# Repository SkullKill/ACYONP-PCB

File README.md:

# ACYONP-PCB
PCB for Access Control Yubikey OTP NFC Pi (ACYONP). For Raspberry Pi. This is a **Door Access Control using Electronic Door Strike, with Yubikey OTP via NFC / KeyPad / WebInterface for Authentication.**

Web interface shows the status of the whole system, along with the ability to enter pin/password/yubikey OTP string for authentication to unlock the door

Uses Inturrupt and Threads to minimise overhead, and to be non blocking as much as possible.

All options are completely customizable through the ini config file

The script [ACYONP](https://github.com/SkullKill/ACYONP) is design specificly for the Raspberry Pi.

SKaccess by Simon Kong

https://www.skaccess.com

ACYONP-SMD-01.jpg
NFC Reader is at the top of the Box, inside. putting the yubikey on top of the box will scan the yubikey neo / yubikey 5 nfc.

ACYONP-webinterface-01.jpg

## V 1.0 21/05/2019 - Initial Release

  ------------------------------------------------------------
## PCB Board Used

Ready to use PCB Board

https://www.skstore.com.au/electronics/pcb/ACYONP

PCB Design Files / gerber files

[ACYONP-PCB](https://github.com/SkullKill/ACYONP-PCB)

FYI Gerber files are in the release section

https://github.com/SkullKill/ACYONP-PCB/releases

more pictures in the wiki

https://github.com/SkullKill/ACYONP-PCB/wiki

ACYONP-SMD-Front-Red-RT-V1.2.jpg

ACYONP-SMD-Back-Red-V1.2.jpg

  ------------------------------------------------------------
## Schematics

ACYONP-SMD-schematics-v1.2a.jpg

------------------------------------------------------------
## Code Used

[ACYONP](https://github.com/SkullKill/ACYONP)

------------------------------------------------------------
## Product Used (not included)

### Dupont kit / Jumper Wires
you will need a dupont crimp kit 2.54 / tool
and / or jumper wires

e.g

Crimping Tool: 0.1-1.0 mm² Capacity, 16-28 AWG
https://www.pololu.com/product/1928

Crimp Connector Housings
https://www.pololu.com/category/70/crimp-connector-housings

Female Crimp Pins for 0.1" Housings
https://www.pololu.com/product/1930

Male Crimp Pins for 0.1" Housings
https://www.pololu.com/product/1931

Wires with Pre-Crimped Terminals
https://www.pololu.com/category/71/wires-with-pre-crimped-terminals

Premium Jumper Wires
https://www.pololu.com/category/65/premium-jumper-wires

https://www.futurlec.com/ConnHead.shtml

### Keypad

Metallic Waterproof 3x4 Keypad
https://www.futurlec.com/Keypads.shtml

### PN532 NFC controller in UART mode

e.g

https://www.dfrobot.com/product-892.html

https://wiki.dfrobot.com/NFC_Module_for_Arduino__SKU_DFR0231_

### Yubico Yubikey
YubiKey 5 NFC

https://www.yubico.com/product/yubikey-5-nfc

### other items used, can be any other ones.

H0307 • 145Lx105Wx65Dmm IP65 Sealed ABS Enclosure

https://www.altronics.com.au/p/h0307-ritec-145lx105wx65dmm-ip65-sealed-abs-enclosure/

H0151 • UB1 (157Lx95Wx53Hmm) Grey ABS Jiffy Box

https://www.altronics.com.au/p/h0151-ub1-157lx95wx53hmm-grey-abs-jiffy-box/

P0628 • 2.1mm Female Plastic Chassis Mount DC Power Socket (not necessary)

https://www.altronics.com.au/p/p0628-2.1mm-female-plastic-chassis-mount-dc-power-socket/

H1554 • 5mm LED Mounts Pk 100

https://www.altronics.com.au/p/h1554-5mm-led-mounts-pk-100/

S6109 • 1.5-24V Piezo Chassis Mount Buzzer (status buzzer)

https://www.altronics.com.au/p/s6109-1.5-24v-piezo-chassis-mount-buzzer/

S6100 • 3-15V Mechanical Chassis Mount Buzzer (door buzzer)

https://www.altronics.com.au/p/s6100-3-15v-mechanical-chassis-mount-buzzer/

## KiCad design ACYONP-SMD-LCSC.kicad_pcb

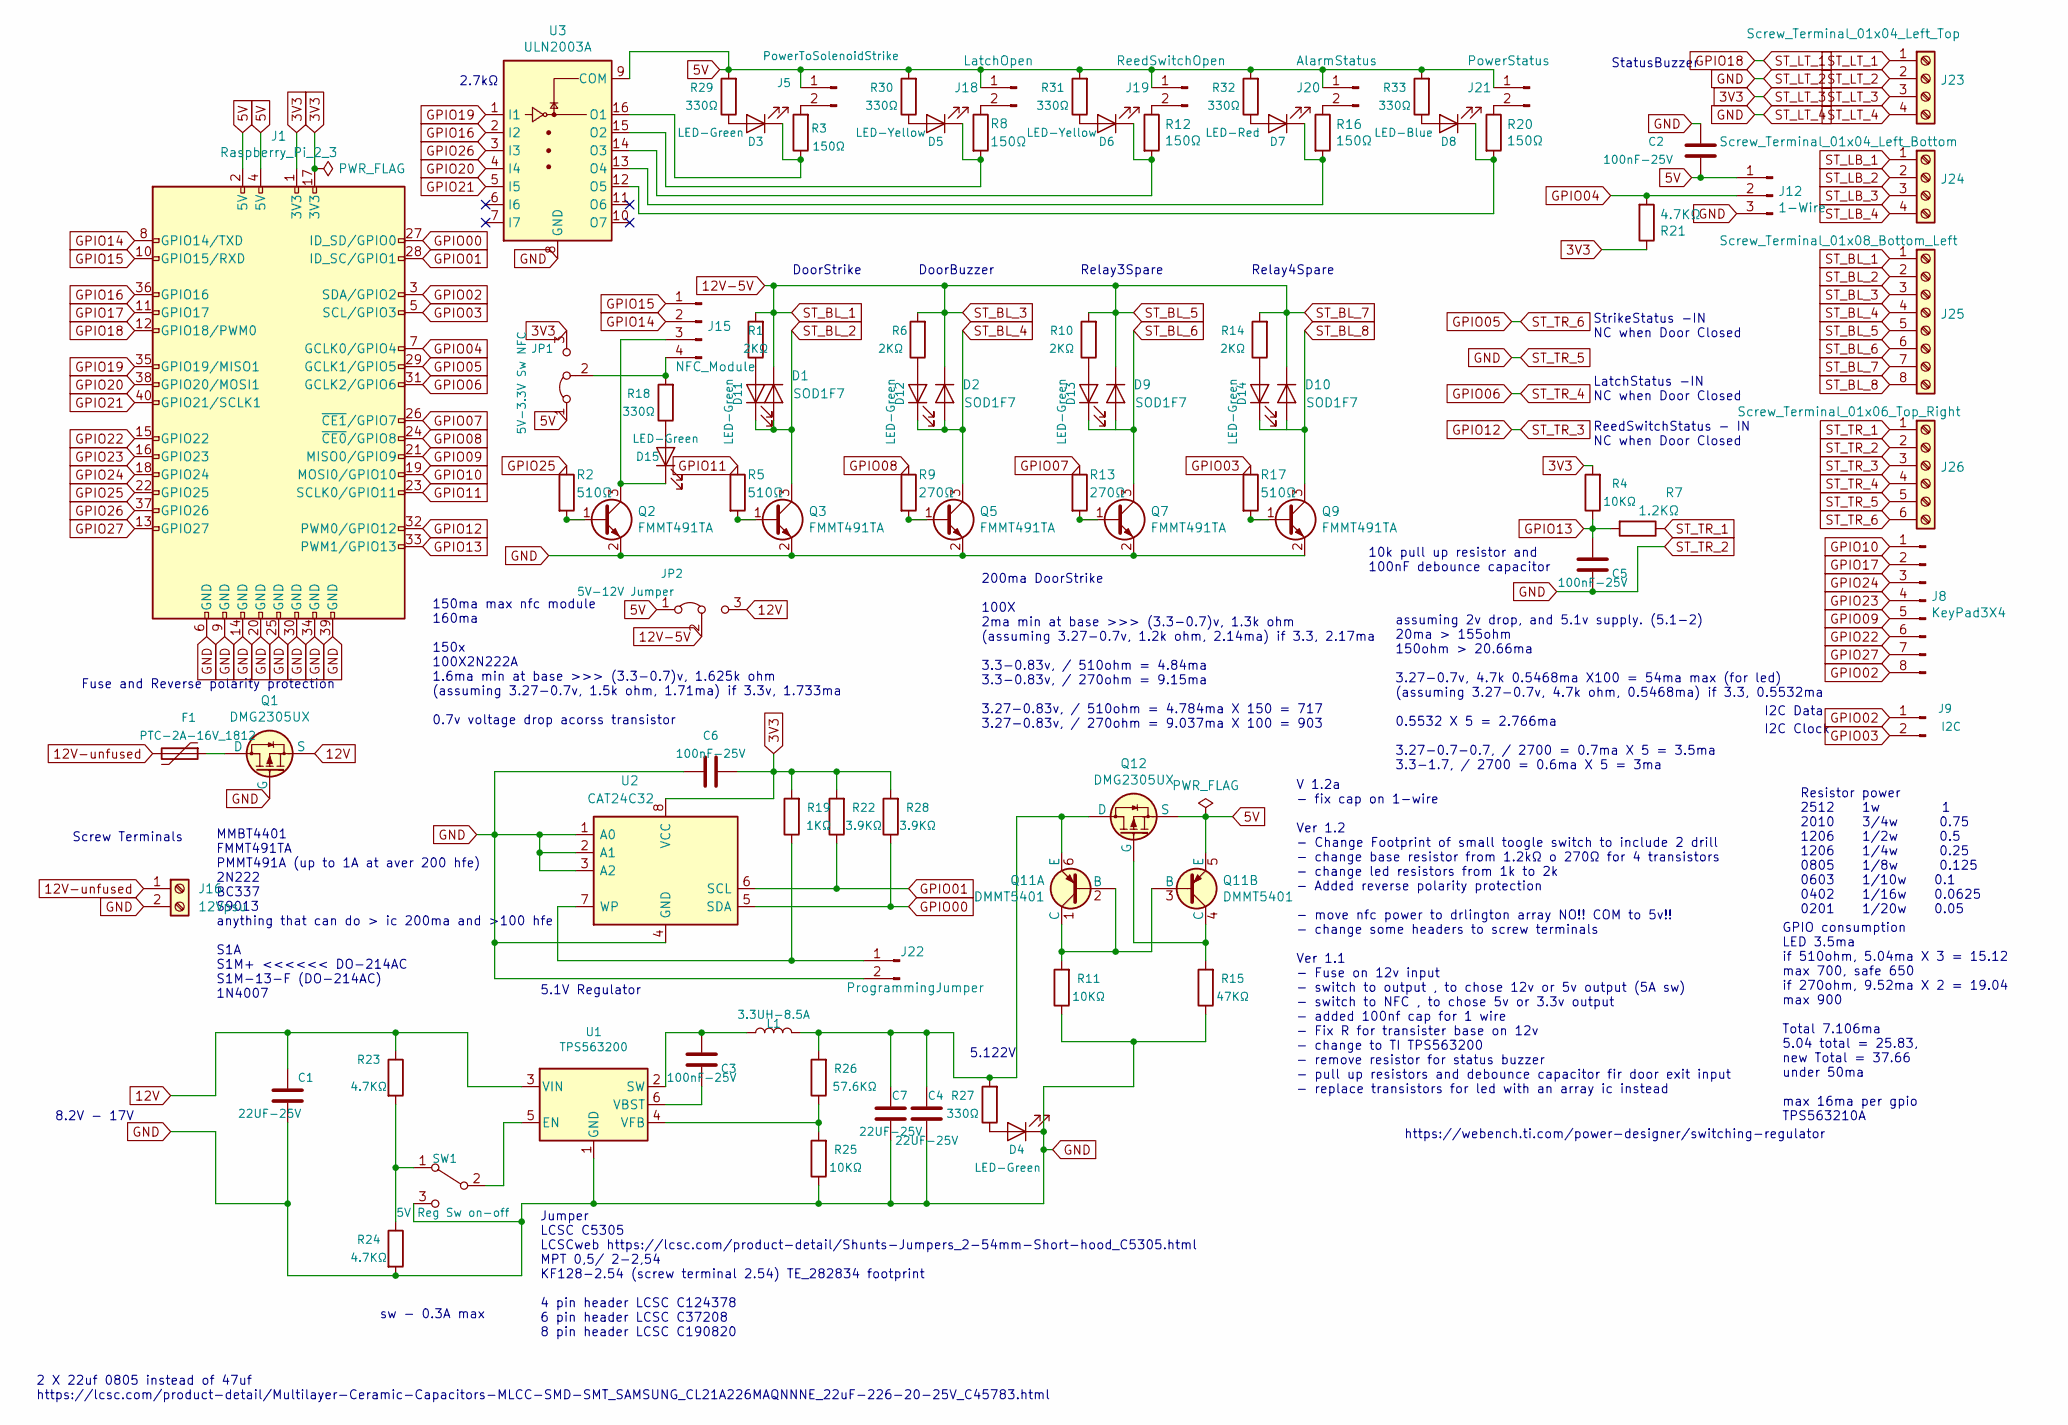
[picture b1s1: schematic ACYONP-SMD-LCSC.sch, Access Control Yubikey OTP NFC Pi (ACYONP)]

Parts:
C1, C4, C7: 22UF-25V; C_0805_2012Metric_Pad1.15x1.40mm_HandSolder; MPN CL21A226MAQNNNE; LCSC C45783
C2, C3, C5, C6: 100nF-25V; C_0805_2012Metric_Pad1.15x1.40mm_HandSolder; MPN GRM21BR71E104KA01L; LCSC C86041
D1, D9, D10: SOD1F7; D_SOD-123; MPN SOD1F7; LCSC C33221
D2: SOD1F7; D_SOD-123
D3, D4, D11, D12, D13, D14, D15: LED-Green; LED_0805_2012Metric_Pad1.15x1.40mm_HandSolder; MPN FC-2012UGK-520D5; LCSC C84260
D5, D6: LED-Yellow; LED_0805_2012Metric_Pad1.15x1.40mm_HandSolder; MPN FC-2012HYK-588J; LCSC C84261
D7: LED-Red; LED_0805_2012Metric_Pad1.15x1.40mm_HandSolder; MPN FC-2012HRK-620D; LCSC C84256
D8: LED-Blue; LED_0805_2012Metric_Pad1.15x1.40mm_HandSolder; MPN FC-A2012BK-470H2; LCSC C84259
F1: PTC-2A-16V_1812; Fuse_1812_4532Metric_Pad1.30x3.40mm_HandSolder; MPN SCF200-16-1812R; LCSC C305617
J1: Raspberry_Pi_2_3; PinSocket_2x20_P2.54mm_Vertical; LCSC C50982
J5: PowerToSolenoidStrike; PinHeader_1x02_P2.54mm_Vertical; LCSC C124375
J8: KeyPad3X4; PinHeader_1x08_P2.54mm_Vertical; LCSC C124381
J9: I2C; PinHeader_1x02_P2.54mm_Vertical; LCSC C124375
J12: 1-Wire; PinHeader_1x03_P2.54mm_Vertical; LCSC C49257
J15: NFC_Module; PinHeader_1x04_P2.54mm_Vertical; LCSC C124378
J16: 12Vpsu; TerminalBlock_bornier-2_P5.08mm; MPN WJ126V-5.0-2P; LCSC C8404
J18: LatchOpen; PinHeader_1x02_P2.54mm_Vertical; LCSC C124375
J19: ReedSwitchOpen; PinHeader_1x02_P2.54mm_Vertical; LCSC C124375
J20: AlarmStatus; PinHeader_1x02_P2.54mm_Vertical; LCSC C124375
J21: PowerStatus; PinHeader_1x02_P2.54mm_Vertical; LCSC C124375
J22: ProgrammingJumper; PinHeader_1x02_P2.54mm_Vertical; LCSC C124375
J23: Screw_Terminal_01x04_Left_Top; TerminalBlock_TE_282834-4_1x04_P2.54mm_Horizontal; MPN KF128-2.54-4P
J24: Screw_Terminal_01x04_Left_Bottom; TerminalBlock_TE_282834-4_1x04_P2.54mm_Horizontal; MPN KF128-2.54-4P
J25: Screw_Terminal_01x08_Bottom_Left; TerminalBlock_TE_282834-8_1x08_P2.54mm_Horizontal; MPN KF128-2.54-8P
J26: Screw_Terminal_01x06_Top_Right; TerminalBlock_TE_282834-6_1x06_P2.54mm_Horizontal; MPN KF128-2.54-6P
JP1: 5V-3.3V Sw NFC; PinHeader_1x03_P2.54mm_Vertical; LCSC C49257
JP2: 5V-12V Jumper; PinHeader_1x03_P2.54mm_Vertical; LCSC C49257
L1: 3.3UH-8.5A; L_6.3x6.3_H3_HandSolder; MPN MPCA-0630-3R3-M; LCSC C268402
Q1, Q12: DMG2305UX; SOT-23; MPN DMG2305UX-13; LCSC C144153
Q2, Q3: FMMT491TA; SOT-23; MPN FMMT491TA; LCSC C141788
Q5, Q7, Q9: FMMT491TA; SOT-23
Q11: DMMT5401; SOT-23-6; MPN DMMT5401-7-F; LCSC C154733
R1, R6, R10, R14: 2KΩ; R_0805_2012Metric_Pad1.15x1.40mm_HandSolder; MPN RC0805FR-072KL; LCSC C114572
R2, R5: 510Ω; R_0805_2012Metric_Pad1.15x1.40mm_HandSolder; MPN RC0805FR-07510RL; LCSC C114563
R3: 150Ω; R_0805_2012Metric_Pad1.15x1.40mm_HandSolder; MPN RC0805FR-07150RL; LCSC C114523
R4, R11, R25: 10KΩ; R_0805_2012Metric_Pad1.15x1.40mm_HandSolder; MPN RC0805DR-0710KL; LCSC C163503
R7: 1.2KΩ; R_0805_2012Metric_Pad1.15x1.40mm_HandSolder; MPN RC0805FR-071K2L; LCSC C114526
R8, R12, R16, R20: 150Ω; R_0805_2012Metric_Pad1.15x1.40mm_HandSolder
R9: 270Ω; R_0805_2012Metric_Pad1.15x1.40mm_HandSolder; MPN RC0805FR-07270RL; LCSC C137558
R13: 270Ω; R_0805_2012Metric_Pad1.15x1.40mm_HandSolder
R15: 47KΩ; R_0805_2012Metric_Pad1.15x1.40mm_HandSolder; MPN RC0805FR-0747KL; LCSC C126351
R17: 510Ω; R_0805_2012Metric_Pad1.15x1.40mm_HandSolder
R18, R27, R29, R30, R31, R32, R33: 330Ω; R_0805_2012Metric_Pad1.15x1.40mm_HandSolder; MPN RC0805FR-07330RL; LCSC C105878
R19: 1KΩ; R_0805_2012Metric_Pad1.15x1.40mm_HandSolder; MPN RC0805FR-071KL; LCSC C95781
R21: 4.7KΩ; R_0805_2012Metric_Pad1.15x1.40mm_HandSolder; MPN RC0805FR-074K7L; LCSC C60816
R22, R28: 3.9KΩ; R_0805_2012Metric_Pad1.15x1.40mm_HandSolder; MPN RC0805FR-073K9L; LCSC C114221
R23, R24: 4.7KΩ; R_0805_2012Metric_Pad1.15x1.40mm_HandSolder
R26: 57.6KΩ; R_0805_2012Metric_Pad1.15x1.40mm_HandSolder; MPN RC0805FR-0757K6L; LCSC C163405
SW1: 5V Reg Sw on-off; SW_SPDT_PCM12; MPN K3-1292S-P2; LCSC C145853
U1: TPS563200; SOT-23-6_Handsoldering; MPN TPS563200DDCR; LCSC C97253
U2: CAT24C32; SOIC-8_3.9x4.9mm_P1.27mm; MPN CAT24C32WI-GT3; LCSC C81193
U3: ULN2003A; SOIC-16_ti-Package-D; MPN ULN2003ADR; LCSC C7512

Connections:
3V3: C6.2, J1.1 (3V3), J1.17 (3V3), J23.3, JP1.3 (B), R4.2, R19.2, R21.1, R22.2, R28.2, U2.8 (VCC)
5V: C2.1, J1.2 (5V), J1.4 (5V), J5.1, J12.1, J18.1, J19.1, J20.1, J21.1, JP1.1 (A), JP2.1 (A), Q11.5 (E), Q12.2 (S), R29.2, R30.2, R31.2, R32.2, R33.2, U3.9 (COM)
12V: C1.2, JP2.3 (B), Q1.2 (S), R23.1, U1.3 (VIN)
12V-5V: D1.1 (K), D2.1 (K), D9.1 (K), D10.1 (K), J25.1, J25.3, J25.5, J25.7, JP2.2 (C), R1.2, R6.2, R10.2, R14.2
12V-unfused: F1.2, J16.1
GND: C1.1, C2.2, C4.2, C5.2, C6.1, C7.2, D4.1 (K), J1.6 (GND), J1.9 (GND), J1.14 (GND), J1.20 (GND), J1.25 (GND), J1.30 (GND), J1.34 (GND), J1.39 (GND), J12.3, J16.2, J22.2, J23.2, J23.4, J26.2, J26.5, Q1.1 (G), Q2.2 (E), Q3.2 (E), Q5.2 (E), Q7.2 (E), Q9.2 (E), R11.1, R15.1, R24.2, R25.1, SW1.3 (C), U1.1 (GND), U2.1 (A0), U2.2 (A1), U2.3 (A2), U2.4 (GND), U3.8 (GND)
GPIO00: J1.27 (ID_SD/GPIO0), R28.1, U2.5 (SDA)
GPIO01: J1.28 (ID_SC/GPIO1), R22.1, U2.6 (SCL)
GPIO02: J1.3 (SDA/GPIO2), J8.8, J9.1
GPIO03: J1.5 (SCL/GPIO3), J9.2, R17.1
GPIO04: J1.7 (GCLK0/GPIO4), J12.2, R21.2
GPIO05: J1.29 (GCLK1/GPIO5), J26.6
GPIO06: J1.31 (GCLK2/GPIO6), J26.4
GPIO07: J1.26 (~CE1~/GPIO7), R13.1
GPIO08: J1.24 (~CE0~/GPIO8), R9.1
GPIO09: J1.21 (MISO0/GPIO9), J8.5
GPIO10: J1.19 (MOSI0/GPIO10), J8.1
GPIO11: J1.23 (SCLK0/GPIO11), R5.1
GPIO12: J1.32 (PWM0/GPIO12), J26.3
GPIO13: C5.1, J1.33 (PWM1/GPIO13), R4.1, R7.2
GPIO14: J1.8 (GPIO14/TXD), J15.2
GPIO15: J1.10 (GPIO15/RXD), J15.1
GPIO16: J1.36 (GPIO16), U3.2 (I2)
GPIO17: J1.11 (GPIO17), J8.2
GPIO18: J1.12 (GPIO18/PWM0), J23.1
GPIO19: J1.35 (GPIO19/MISO1), U3.1 (I1)
GPIO20: J1.38 (GPIO20/MOSI1), U3.4 (I4)
GPIO21: J1.40 (GPIO21/SCLK1), U3.5 (I5)
GPIO22: J1.15 (GPIO22), J8.6
GPIO23: J1.16 (GPIO23), J8.4
GPIO24: J1.18 (GPIO24), J8.3
GPIO25: J1.22 (GPIO25), R2.1
GPIO26: J1.37 (GPIO26), U3.3 (I3)
GPIO27: J1.13 (GPIO27), J8.7
unnamed: C3.1, L1.1, U1.2 (SW)
unnamed: C3.2, U1.6 (VBST)
unnamed: C4.1, C7.1, L1.2, Q11.6 (E), Q12.3 (D), R26.2, R27.2
unnamed: D3.1 (K), R3.1, U3.16 (O1)
unnamed: D3.2 (A), R29.1
unnamed: D4.2 (A), R27.1
unnamed: D5.1 (K), R8.2, U3.15 (O2)
unnamed: D5.2 (A), R30.1
unnamed: D6.1 (K), R12.2, U3.14 (O3)
unnamed: D6.2 (A), R31.1
unnamed: D7.1 (K), R16.2, U3.13 (O4)
unnamed: D7.2 (A), R32.1
unnamed: D8.1 (K), R20.2, U3.12 (O5)
unnamed: D8.2 (A), R33.1
unnamed: D11.2 (A), R1.1
unnamed: D12.2 (A), R6.1
unnamed: D13.2 (A), R10.1
unnamed: D14.2 (A), R14.1
unnamed: D15.1 (K), J15.3, Q2.3 (C)
unnamed: D15.2 (A), R18.1
unnamed: F1.1, Q1.3 (D)
unnamed: J5.2, R3.2
unnamed: J15.4, JP1.2 (C), R18.2
unnamed: J18.2, R8.1
unnamed: J19.2, R12.1
unnamed: J20.2, R16.1
unnamed: J21.2, R20.1
unnamed: J22.1, R19.1, U2.7 (WP)
unnamed: Q2.1 (B), R2.2
unnamed: Q3.1 (B), R5.2
unnamed: Q5.1 (B), R9.2
unnamed: Q7.1 (B), R13.2
unnamed: Q9.1 (B), R17.2
unnamed: Q11.1 (C), Q11.2 (B), Q11.3 (B), R11.2
unnamed: Q11.4 (C), Q12.1 (G), R15.2
unnamed: R23.2, R24.1, SW1.1 (A)
unnamed: R25.2, R26.1, U1.4 (VFB)
unnamed: SW1.2 (B), U1.5 (EN)
ST_BL_2: D1.2 (A), D11.1 (K), J25.2, Q3.3 (C)
ST_BL_4: D2.2 (A), D12.1 (K), J25.4, Q5.3 (C)
ST_BL_6: D9.2 (A), D13.1 (K), J25.6, Q7.3 (C)
ST_BL_8: D10.2 (A), D14.1 (K), J25.8, Q9.3 (C)
ST_TR_1: J26.1, R7.1

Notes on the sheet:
assuming 2v drop, and 5.1v supply. (5.1-2) 20ma > 155ohm 150ohm > 20.66ma 3.27-0.7v, 4.7k 0.5468ma X100 = 54ma max (for led) (assuming 3.27-0.7v, 4.7k ohm, 0.5468ma) if 3.3, 0.5532ma 0.5532 X 5 = 2.766ma 3.27-0.7-0.7, / 2700 = 0.7ma X 5 = 3.5ma 3.3-1.7, / 2700 = 0.6ma X 5 = 3ma
200ma DoorStrike 100X 2ma min at base >>> (3.3-0.7)v, 1.3k ohm (assuming 3.27-0.7v, 1.2k ohm, 2.14ma) if 3.3, 2.17ma 3.3-0.83v, / 510ohm = 4.84ma 3.3-0.83v, / 270ohm = 9.15ma 3.27-0.83v, / 510ohm = 4.784ma X 150 = 717 3.27-0.83v, / 270ohm = 9.037ma X 100 = 903
StrikeStatus -IN NC when Door Closed
LatchStatus -IN NC when Door Closed
ReedSwitchStatus - IN NC when Door Closed
Screw Terminals
MMBT4401 FMMT491TA PMMT491A (up to 1A at aver 200 hfe) 2N222 BC337 S9013 anything that can do > ic 200ma and >100 hfe S1A S1M+ <<<<<< DO-214AC S1M-13-F (DO-214AC) 1N4007
https://webench.ti.com/power-designer/switching-regulator
V 1.2a - fix cap on 1-wire Ver 1.2 - Change Footprint of small toogle switch to include 2 drill - change base resistor from 1.2kΩ o 270Ω for 4 transistors - change led resistors from 1k to 2k - Added reverse polarity protection - move nfc power to drlington array NO!! COM to 5v!! - change some head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
10k pull up resistor and 100nF debounce capacitor
I2C Data
I2C Clock
GPIO consumption LED 3.5ma if 510ohm, 5.04ma X 3 = 15.12 max 700, safe 650 if 270ohm, 9.52ma X 2 = 19.04 max 900 Total 7.106ma 5.04 total = 25.83, new Total = 37.66 under 50ma max 16ma per gpio TPS563210A
5.122V
5.1V Regulator
8.2V - 17V
sw - 0.3A max
Jumper LCSC C5305 LCSCweb https://lcsc.com/product-detail/Shunts-Jumpers_2-54mm-Short-hood_C5305.html MPT 0,5/ 2-2,54 KF128-2.54 (screw terminal 2.54) TE_282834 footprint 4 pin header LCSC C124378 6 pin header LCSC C37208 8 pin header LCSC C190820
2 X 22uf 0805 instead of 47uf https://lcsc.com/product-detail/Multilayer-Ceramic-Capacitors-MLCC-SMD-SMT_SAMSUNG_CL21A226MAQNNNE_22uF-226-20-25V_C45783.html
2.7kΩ
Fuse and Reverse polarity protection
Resistor power 2512 1w 1 2010 3/4w 0.75 1206 1/2w 0.5 1206 1/4w 0.25 0805 1/8w 0.125 0603 1/10w 0.1 0402 1/16w 0.0625 0201 1/20w 0.05
150ma max nfc module 160ma 150x 100X2N222A 1.6ma min at base >>> (3.3-0.7)v, 1.625k ohm (assuming 3.27-0.7v, 1.5k ohm, 1.71ma) if 3.3v, 1.733ma 0.7v voltage drop acorss transistor
Relay4Spare
DoorStrike
DoorBuzzer
Relay3Spare
StatusBuzzer

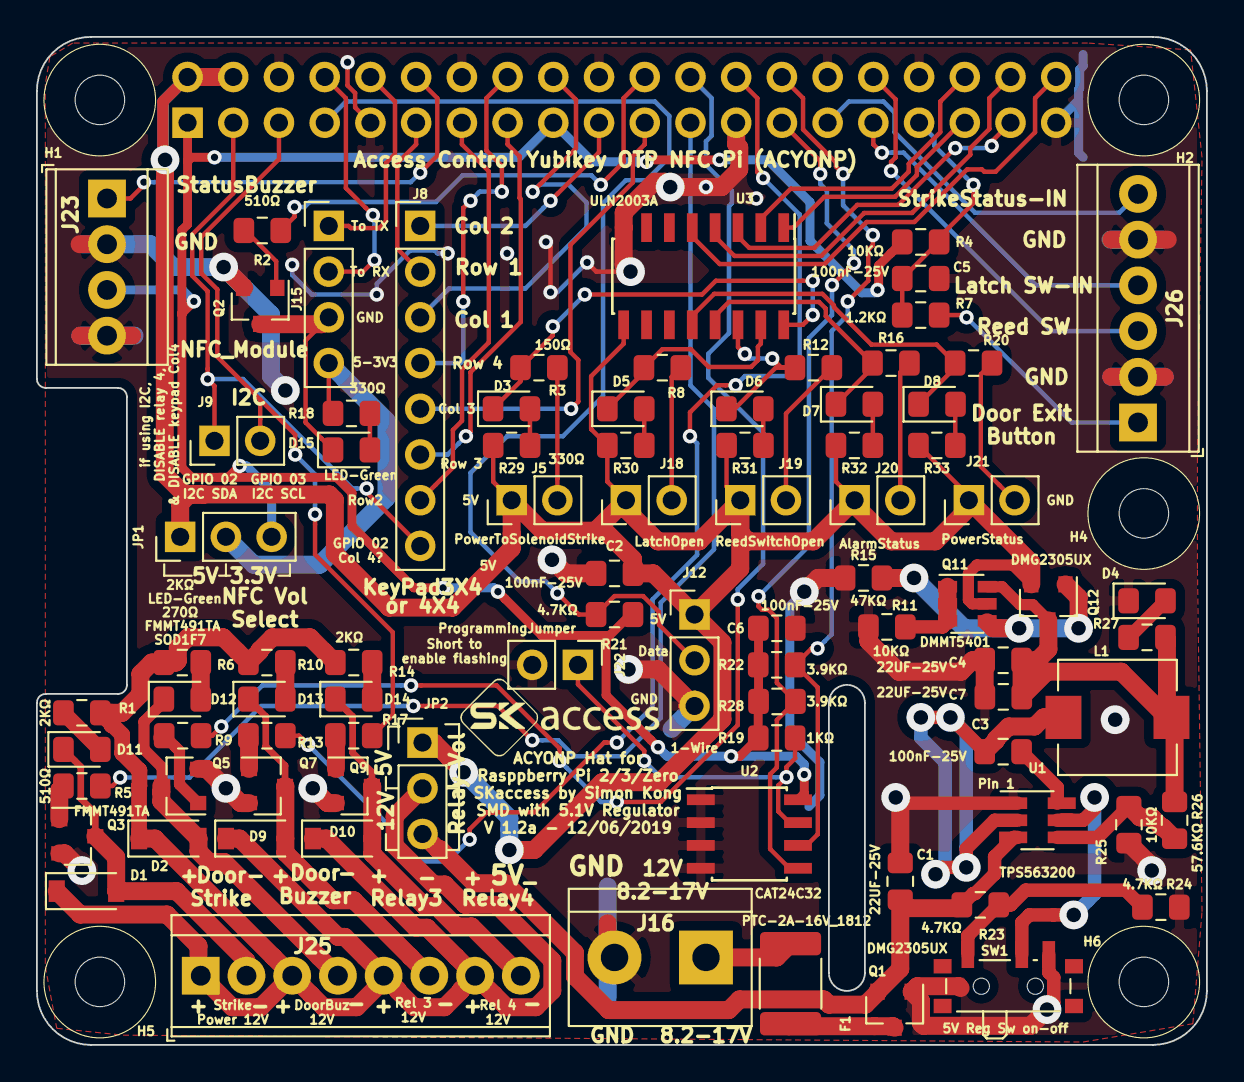
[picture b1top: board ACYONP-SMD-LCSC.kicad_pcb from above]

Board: 2 copper layers, 65.0 x 56.0 mm, 91 parts (1 on the bottom side), 77 nets.

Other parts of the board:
H1, H2, H4, H5, H6: MountingHole; MountingHole_2.75mm_M2.5_NoPad

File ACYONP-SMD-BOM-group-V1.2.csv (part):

Reference, Quantity, Value, Footprint, Datasheet, LCSC, LCSCweb, ALT, MPN, Alt, MPNweb, web
C2 C5 C3 C6 ,4,"100nF-25V","Capacitor_SMD:C_0805_2012Metric_Pad1.15x1.40mm_HandSolder","https://datasheet.lcsc.com/szlcsc/Murata-Electronics-GRM21BR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","C86041","https://lcsc.com/product-detail/Multilayer-Ceramic-Capacitor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","","GRM21BR71E104KA01L","","",""
C4 C1 C7 ,3,"22UF-25V","Capacitor_SMD:C_0805_2012Metric_Pad1.15x1.40mm_HandSolder","https://datasheet.lcsc.com/szlcsc/Samsung-Electro-Mechanics-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","C45783","https://lcsc.com/product-detail/Multilayer-Ceramic-Capacitor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","C86816","CL21A226MAQNNNE","","",""
D1 D10 D9 D2 ,4,"SOD1F7","Diode_SMD:D_SOD-123","https://datasheet.lcsc.com/szlcsc/1903041730_MDD-Jiangsu-Yut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","C33221","https://lcsc.com/product-detail/Diodes-Rectifiers-Fast-Recov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","","SOD1F7","","",""
D3 D4 D11 D12 D13 D14 D15 ,7,"LED-Green","LED_SMD:LED_0805_2012Metric_Pad1.15x1.40mm_HandSolder","https://datasheet.lcsc.com/szlcsc/Foshan-NationStar-Optoelec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","C84260","https://lcsc.com/product-detail/Light-Emitting-Diodes-LED_Em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","","FC-2012UGK-520D5","","",""
D5 D6 ,2,"LED-Yellow","LED_SMD:LED_0805_2012Metric_Pad1.15x1.40mm_HandSolder","https://datasheet.lcsc.com/szlcsc/Foshan-NationStar-Optoelec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","C84261","https://lcsc.com/product-detail/Light-Emitting-Diodes-LED_Ye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","","FC-2012HYK-588J","","",""
D7 ,1,"LED-Red","LED_SMD:LED_0805_2012Metric_Pad1.15x1.40mm_HandSolder","https://datasheet.lcsc.com/szlcsc/Foshan-NationStar-Optoelec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","C84256","https://lcsc.com/product-detail/Light-Emitting-Diodes-LED_Re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","","FC-2012HRK-620D","","",""
D8 ,1,"LED-Blue","LED_SMD:LED_0805_2012Metric_Pad1.15x1.40mm_HandSolder","https://datasheet.lcsc.com/szlcsc/Foshan-NationStar-Optoelec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","C84259","https://lcsc.com/product-detail/Light-Emitting-Diodes-LED_Bl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","","FC-A2012BK-470H2","","",""
F1 ,1,"PTC-2A-16V_1812","Fuse:Fuse_1812_4532Metric_Pad1.30x3.40mm_HandSolder","https://datasheet.lcsc.com/szlcsc/SOCAY-Elec-SCF200-16-1812R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","C305617","https://lcsc.com/product-detail/Others_SOCAY-Elec-SCF200-16-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","","SCF200-16-1812R","","",""
J1 ,1,"Raspberry_Pi_2_3","Connector_PinSocket_2.54mm:PinSocket_2x20_P2.54mm_Vertical","https://www.raspberrypi.org/documentation/hardware/raspberry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","C50982","https://lcsc.com/product-detail/Pin-Header-Female-Header_Boo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","","","C35165","",""
J12 ,1,"1-Wire","Connector_PinHeader_2.54mm:PinHeader_1x03_P2.54mm_Vertical","https://datasheet.lcsc.com/szlcsc/Boom-Precision-Elec-Header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","C49257","https://lcsc.com/product-detail/Pin-Header-Female-Header_Boo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","","","","",""
J15 ,1,"NFC_Module","Connector_PinHeader_2.54mm:PinHeader_1x04_P2.54mm_Vertical","https://datasheet.lcsc.com/szlcsc/Shenzhen-Cankemeng-Headers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","C124378","https://lcsc.com/product-detail/Pin-Header-Female-Header_She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","","","","",""
J16 ,1,"12Vpsu","TerminalBlock:TerminalBlock_bornier-2_P5.08mm","https://datasheet.lcsc.com/szlcsc/Ningbo-Kangnex-Elec-WJ126V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","C8404","https://lcsc.com/product-detail/Pluggable-System-Terminal-Bl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","","WJ126V-5.0-2P","","",""
J18 ,1,"LatchOpen","Connector_PinHeader_2.54mm:PinHeader_1x02_P2.54mm_Vertical","~","C124375","","","","","",""
J19 ,1,"ReedSwitchOpen","Connector_PinHeader_2.54mm:PinHeader_1x02_P2.54mm_Vertical","~","C124375","","","","","",""
J20 ,1,"AlarmStatus","Connector_PinHeader_2.54mm:PinHeader_1x02_P2.54mm_Vertical","~","C124375","","","","","",""
J21 ,1,"PowerStatus","Connector_PinHeader_2.54mm:PinHeader_1x02_P2.54mm_Vertical","~","C124375","","","","","",""
J22 ,1,"ProgrammingJumper","Connector_PinHeader_2.54mm:PinHeader_1x02_P2.54mm_Vertical","~","C124375","","","","","",""
J23 ,1,"Screw_Terminal_01x04_Left_Top","TerminalBlock_TE-Connectivity:TerminalBlock_TE_282834-4_1x04_P2.54mm_Horizontal","~","","","","KF128-2.54-4P","","http://en.cnkefa.com/index.php?c=product&id=159","https://www.aliexpress.com/store/group/Connection-terminal/4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"
J24 ,1,"Screw_Terminal_01x04_Left_Bottom","TerminalBlock_TE-Connectivity:TerminalBlock_TE_282834-4_1x04_P2.54mm_Horizontal","~","","","","KF128-2.54-4P","","http://en.cnkefa.com/index.php?c=product&id=159","https://www.aliexpress.com/store/group/Connection-terminal/4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"
J25 ,1,"Screw_Terminal_01x08_Bottom_Left","TerminalBlock_TE-Connectivity:TerminalBlock_TE_282834-8_1x08_P2.54mm_Horizontal","~","","","","KF128-2.54-8P","","http://en.cnkefa.com/index.php?c=product&id=159",""
J26 ,1,"Screw_Terminal_01x06_Top_Right","TerminalBlock_TE-Connectivity:TerminalBlock_TE_282834-6_1x06_P2.54mm_Horizontal","~","","","","KF128-2.54-6P","","http://en.cnkefa.com/index.php?c=product&id=159",""
J5 ,1,"PowerToSolenoidStrike","Connector_PinHeader_2.54mm:PinHeader_1x02_P2.54mm_Vertical","https://datasheet.lcsc.com/szlcsc/Shenzhen-Cankemeng-Headers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","C124375","https://lcsc.com/product-detail/Pin-Header-Female-Header_She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","","","","",""
J8 ,1,"KeyPad3X4","Connector_PinHeader_2.54mm:PinHeader_1x08_P2.54mm_Vertical","https://datasheet.lcsc.com/szlcsc/Shenzhen-Cankemeng-Headers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","C124381","https://lcsc.com/product-detail/Pin-Header-Female-Header_She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","","","","",""
J9 ,1,"I2C","Connector_PinHeader_2.54mm:PinHeader_1x02_P2.54mm_Vertical","~","C124375","","","","","",""
JP1 ,1,"5V-3.3V Sw NFC","Connector_PinHeader_2.54mm:PinHeader_1x03_P2.54mm_Vertical","https://datasheet.lcsc.com/szlcsc/Boom-Precision-Elec-Header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","C49257","https://lcsc.com/product-detail/Pin-Header-Female-Header_Boo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","","","","",""
JP2 ,1,"5V-12V Jumper","Connector_PinHeader_2.54mm:PinHeader_1x03_P2.54mm_Vertical","https://datasheet.lcsc.com/szlcsc/Boom-Precision-Elec-Header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","C49257","https://lcsc.com/product-detail/Pin-Header-Female-Header_Boo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","","","","",""
L1 ,1,"3.3UH-8.5A","ACYONP-SMD-LCSC:L_6.3x6.3_H3_HandSolder","https://datasheet.lcsc.com/szlcsc/1812181433_MAZO-MPCA-0630-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","C268402","https://lcsc.com/product-detail/Others_MAZO-MPCA-0630-3R3-M_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","C207839","MPCA-0630-3R3-M","","",""
Q11 ,1,"DMMT5401","Package_TO_SOT_SMD:SOT-23-6","https://datasheet.lcsc.com/szlcsc/Diodes-Incorporated-DMMT54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","C154733","https://lcsc.com/product-detail/Transistors-NPN-PNP_DIODES_D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","","DMMT5401-7-F","","",""
Q12 Q1 ,2,"DMG2305UX","Package_TO_SOT_SMD:SOT-23","https://datasheet.lcsc.com/szlcsc/Diodes-Incorporated-DMG230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","C144153","https://lcsc.com/product-detail/MOSFET_Diodes-Incorporated_D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","","DMG2305UX-13","","",""
Q3 Q5 Q7 Q9 Q2 ,5,"FMMT491TA","Package_TO_SOT_SMD:SOT-23","https://datasheet.lcsc.com/szlcsc/1811291034_Diodes-Incorpor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","C141788","https://lcsc.com/product-detail/Transistors-NPN-PNP_Diodes-I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","","FMMT491TA","","",""
R1 R6 R10 R14 ,4,"2KΩ","Resistor_SMD:R_0805_2012Metric_Pad1.15x1.40mm_HandSolder","https://datasheet.lcsc.com/szlcsc/YAGEO-RC0805FR-072KL_C114572.pdf","C114572","https://lcsc.com/product-detail/Chip-Resistor-Surface-Mount_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","","RC0805FR-072KL","","",""
R15 ,1,"47KΩ","Resistor_SMD:R_0805_2012Metric_Pad1.15x1.40mm_HandSolder","https://datasheet.lcsc.com/szlcsc/YAGEO-RC0805FR-0747KL_C126351.pdf","C126351","https://lcsc.com/product-detail/Chip-Resistor-Surface-Mount_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","","RC0805FR-0747KL","","",""
R19 ,1,"1KΩ","Resistor_SMD:R_0805_2012Metric_Pad1.15x1.40mm_HandSolder","https://datasheet.lcsc.com/szlcsc/YAGEO-RC0805FR-071KL_C95781.pdf","C95781","https://lcsc.com/product-detail/Chip-Resistor-Surface-Mount_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","","RC0805FR-071KL","","",""
R21 R23 R24 ,3,"4.7KΩ","Resistor_SMD:R_0805_2012Metric_Pad1.15x1.40mm_HandSolder","https://datasheet.lcsc.com/szlcsc/YAGEO-RC0805FR-074K7L_C60816.pdf","C60816","https://lcsc.com/product-detail/Chip-Resistor-Surface-Mount_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","","RC0805FR-074K7L","","",""
R22 R28 ,2,"3.9KΩ","Resistor_SMD:R_0805_2012Metric_Pad1.15x1.40mm_HandSolder","https://datasheet.lcsc.com/szlcsc/YAGEO-RC0805FR-073K9L_C114221.pdf","C114221","https://lcsc.com/product-detail/Chip-Resistor-Surface-Mount_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","","RC0805FR-073K9L","","",""
R26 ,1,"57.6KΩ","Resistor_SMD:R_0805_2012Metric_Pad1.15x1.40mm_HandSolder","https://datasheet.lcsc.com/szlcsc/YAGEO-RC0805FR-0757K6L_C16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","C163405","https://lcsc.com/product-detail/Chip-Resistor-Surface-Mount_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","","RC0805FR-0757K6L","","",""
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
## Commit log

2019-07-27 Create test
2019-07-27 initial
